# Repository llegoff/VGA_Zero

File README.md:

[:fr:](LISEZMOI.md) [:uk:](README.md)

# VGA_Zero
VGA interface for Raspberry Pi Zéro &amp; 2,3,B+

for pi400 see https://github.com/llegoff/Pi400VGA

buy rev3 on [ebay](https://www.ebay.fr/itm/154857982971) :package:

### DPI (Display parallel Interface)
Like [VGA666](https://github.com/fenlogic/vga666), this pcb uses dpi interface (in mode 3 to free gpio 18 & 19)

see https://www.raspberrypi.org/documentation/hardware/raspberrypi/dpi/README.md

only the necessary bits of the dpi are redirected to the 40-pin GPIO port, with the [vga565.dtbo](overlays/vga565.dtbo?raw=true) file loaded at startup

here is the code of the file:

    /dts-v1/;
    /plugin/;
    /{
    	compatible = "brcm,bcm2708";
    	// There is no VGA driver module, but we need a platform device
    	// node (that doesn't already use pinctrl) to hang the pinctrl
    	// reference on - leds will do
    	fragment@0 {
    		target = <&leds>;
    		__overlay__ {
    			pinctrl-names = "default";
    			pinctrl-0 = <&vga565_pins>;
    		};
	    };
    	fragment@1 {
    		target = <&gpio>;
    		__overlay__ {
    			vga565_pins: vga565_pins {
        			brcm,pins = <2 3 4 5 6 7 8 12 13 14 15 16 17 20 21 22 23 24>;
    				brcm,function = <6>; /* alt2 */
				    brcm,pull = <0>; /* no pull */
			    };
		    };
	    };
    };

/boot/config.txt
    
    # disable i2c, pin use by h-sync & v-sync
    dtparam=i2c_arm=off
    dtoverlay=vga565
    dpi_output_format=0x13
    enable_dpi_lcd=1
    display_default_lcd=1
    dpi_group=2
    dpi_mode=16
    #---------------- dpi_mode line ---------------------
    #---> 640x480 60hz    dpi_mode=4
    #---> 800x600 60hz    dpi_mode=9
    #---> 1024x768 60hz   dpi_mode=16
    #---> 1280x768 60hz   dpi_mode=23
    #---> 1280x800 60hz   dpi_mode=28
    #---> 1280x960 60hz   dpi_mode=32
    #---> 1280x1024 60hz  dpi_mode=35
    #---> 1360x768 60hz   dpi_mode=39
    #---> 1366x768 60hz   dpi_mode=81
    #---> 1400x1050 60hz  dpi_mode=42
    #---> 1440x900 60hz   dpi_mode=47
    #---> 1600x1200 60hz  dpi_mode=51
    #---> 1680x1050 60hz  dpi_mode=58
    #---> 1920x1080 60hz  dpi_mode=82
    #---> 1920x1200 60hz  dpi_mode=69
    #---> 1920x1440 60hz  dpi_mode=73

alternate config, no need dtbo file

    # replace dtoverlay=vc4-kms-v3d with
    dtoverlay=vc4-fkms-v3d
    # disable i2c, pin use by h-sync & v-sync
    dtparam=i2c_arm=off
    gpio=2-8,12-17,20-24=a2
    dpi_output_format=0x13
    enable_dpi_lcd=1
    display_default_lcd=1
    dpi_group=2
    dpi_mode=16
    #---------------- dpi_mode line ---------------------
    #---> 640x480 60hz    dpi_mode=4
    #---> 800x600 60hz    dpi_mode=9
    #---> 1024x768 60hz   dpi_mode=16
    #---> 1280x768 60hz   dpi_mode=23
    #---> 1280x800 60hz   dpi_mode=28
    #---> 1280x960 60hz   dpi_mode=32
    #---> 1280x1024 60hz  dpi_mode=35
    #---> 1360x768 60hz   dpi_mode=39
    #---> 1366x768 60hz   dpi_mode=81
    #---> 1400x1050 60hz  dpi_mode=42
    #---> 1440x900 60hz   dpi_mode=47
    #---> 1600x1200 60hz  dpi_mode=51
    #---> 1680x1050 60hz  dpi_mode=58
    #---> 1920x1080 60hz  dpi_mode=82
    #---> 1920x1200 60hz  dpi_mode=69
    #---> 1920x1440 60hz  dpi_mode=73

Configuration working with vc4-kms-v3d

    dtoverlay=vc4-kms-dpi-generic,rgb565-padhi
    dtparam=hactive=800,hfp=40,hsync=128,hbp=88
    dtparam=vactive=600,vfp=1,vsync=4,vbp=23
    dtparam=clock-frequency=40000000
    #   Resolution@freq  hactive hfp hsync  hbp vactive vfp vsync vbp  clock-frequency
    #VGA   640x480  @60   640     16   96    48   480    10   2    33    25175000
    #SVGA  800x600  @60   800     40  128    88   600     1   4    23    40000000
    #XGA  1024x768  @60  1024     24  136   160   768     3   6    29    65000000
    #VESA 1368x768  @60  1368     72  144   216   768     1   3    23    85860000
    #VESA 1280x800  @60  1280     64  136   200   800     1   3    24    83460000
    #VESA 1280x1024 @60  1280     48  112   248  1024     1   3    38   108000000
    #VESA 1400x1050 @60  1400     88  152   240  1050     1   3    33   122660000
    #VESA 1600x1200 @60  1600     64  192   304  1200     1   3    46   162000000
    #--- TV -----
    #244p (NTSC res)@60   320      4   30    46   240     4   5    14     6400000
    #288p (PAL res) @50   384     16   32    40   288     3   2    19     7363200
    #480i (NTSC res)@60   640     24   64   104   480     3   6    34    13054080
    #576i (PAL res) @50   768     24   72    88   576     6   5    38    14875000
    #480p           @60   640     24   96    48   480    11   2    32    25452000
    #720p           @60  1280    110   40   220   720     5   5    20    74250000
    #1080p          @60  1920     88   44   148  1080     4   5    36   148500000
    #more timming on http://tinyvga.com/vga-timing

### 15khz cathode ray screen

    # disable i2c, pin use by h-sync & v-sync
    dtparam=i2c_arm=off
    gpio=2-8,12-17,20-24=a2
    dpi_output_format=0x13
    enable_dpi_lcd=1
    display_default_lcd=1
    dpi_group=2
    dpi_mode=87
    #hdmi_timings=506 1 8 48 56 240 1 3 10 6 0 0 0 60 0 9600000 1
    #hdmi_timings=512 1 16 48 64 288 1 3 5 6 0 0 0 50 0 9600000 1
    # Custom 15kHz mode
    hdmi_timings=506 1 8 44 52 240 1 6 10 6 0 0 0 60 0 9600000 1
    #hdmi_timings=320 1 17 33 34 224 1 14 8 18 0 0 0 60 0 6400000 1
    #hdmi_timings=960 0 173 8 0 160 0 40 10 0 0 0 0 60 0 19200000 8
    #hdmi_timings=320 1 25 30 30 240 1 9 3 10 0 0 0 60 0 6400000 1
    #hdmi_timings=1920 1 52 208 260 240 1 6 10 6 0 0 0 60 0 38400000 1
    
for recalbox see https://recalbox.gitbook.io/tutorials/v/francais/video/crt/configurez-votre-ecran-cathodique-sur-le-bus-dpi-vga666-piscart-rgbpi

### Dual Screen (VGA + HDMI)

on the pi4 and pi400, the dual screen function is supported by the vc4 fkms v3d driver

    [pi4]
    # Enable DRM VC4 V3D driver on top of the dispmanx display stack
    dtoverlay=vc4-fkms-v3d
    max_framebuffers=2
    
for previous versions:

:warning: need raspbian buster

edit file /boot/config.txt  

at the end of the file, add line:

    [all]
    #dtoverlay=vc4-fkms-v3d
    max_framebuffers=2

edit file /usr/share/X11/xorg.conf.d/99-fbturbo.conf

     This is a minimal sample config file, which can be copied to
    # /etc/X11/xorg.conf in order to make the Xorg server pick up
    # and load xf86-video-fbturbo driver installed in the system.    
    #
    # When troubleshooting, check /var/log/Xorg.0.log for the debugging
    # output and error messages.
    #
    # Run "man fbturbo" to get additional information about the extra
    # configuration options for tuning the driver.
    
    #Section "Device"
    #        Identifier      "Allwinner A10/A13 FBDEV"
    #        Driver          "fbturbo"
    #        Option          "fbdev" "/dev/fb0"
    #        Option          "SwapbuffersWait" "true"
    #EndSection
    
    Section "Device"
    Identifier "Raspberry Pi HDMI"
    Driver "fbturbo"
    Option "fbdev" "/dev/fb0"
    Option "ShadowFB" "off"
    EndSection
    
    Section "Device"
    Identifier "Raspberry Pi DPI"
    Driver "fbturbo"
    Option "fbdev" "/dev/fb1"
    Option "ShadowFB" "off"
    EndSection
    
    Section "Monitor"
    Identifier "HDMI"
    EndSection

    Section "Monitor"
    Identifier "DPI"
    EndSection
    
    Section "Screen"
    Identifier "screen0"
    Device "Raspberry Pi HDMI"
    Monitor "HDMI"
    EndSection
    
    Section "Screen"
    Identifier "screen1"
    Device "Raspberry Pi DPI"
    Monitor "DPI"
    EndSection
    
    Section "ServerLayout"
    Identifier "default"
    Screen 0 "screen0" 0 0
    Screen 1 "screen1" RightOf "screen0"
    Option "Xinerama" "on"
    EndSection
### Remote Desktop MultiMonitor
install freeRDP

    sudo apt-get install freerdp2-x11

start freeRDP session
    
    xfreerdp /v:<computer name or IP> /u:<user> /d:<domain> /sound:sys:alsa /multimon

or

    xfreerdp /v:<computer name or IP> /u:<user> /d:<domain> /g:<gateway name or IP> /gu:<gateway user> /gd:<gateway domain> /sound:sys:alsa /multimon

### Audio Interface
audio interface is connected to gpio 18 & 19 (PWM)

see https://learn.adafruit.com/adding-basic-audio-ouput-to-raspberry-pi-zero/pi-zero-pwm-audio

/boot/config.txt

    # Enable audio for PiZero(loads snd_bcm2835)
    dtoverlay=pwm-2chan,pin=18,func=2,pin2=19,func2=2
    dtparam=audio=on

For Pi4 or Pi400 use audremap overlay

/boot/config.txt

    # Enable audio for PiZero(loads snd_bcm2835)
    dtoverlay=audremap,pins_18_19
    dtparam=audio=on

### SPI Interface
GPIO 9 , 10, 11 , 25, 26, 27 can be used as SPI , whit overlay spi0-cs, with CS redirection to gpio 26 & 27

/boot/config.txt

    # uncomment to use spi0 with cs0 & cs1 retirected on pin 26 & 27 
    dtparam=spi=on
    dtoverlay=spi0-cs,cs0_pin=26,cs1_pin=27

## Schematic

## PCB

## Installation
Copy [vga565.dtbo](overlays/vga565.dtbo?raw=true) to /boot/overlays/
and copy content of [config-example.txt](overlays/config-example.txt?raw=true) to /boot/config.txt

## Révision
rev1
- bad vga footprint, hole too small

rev2
- change vga footprint
- move j3 & j5

rev3
- add GPIO25 to J4 connector
- add j6 DC 3.5x1.3 connector
- change to Kicad v5.0.2 lib

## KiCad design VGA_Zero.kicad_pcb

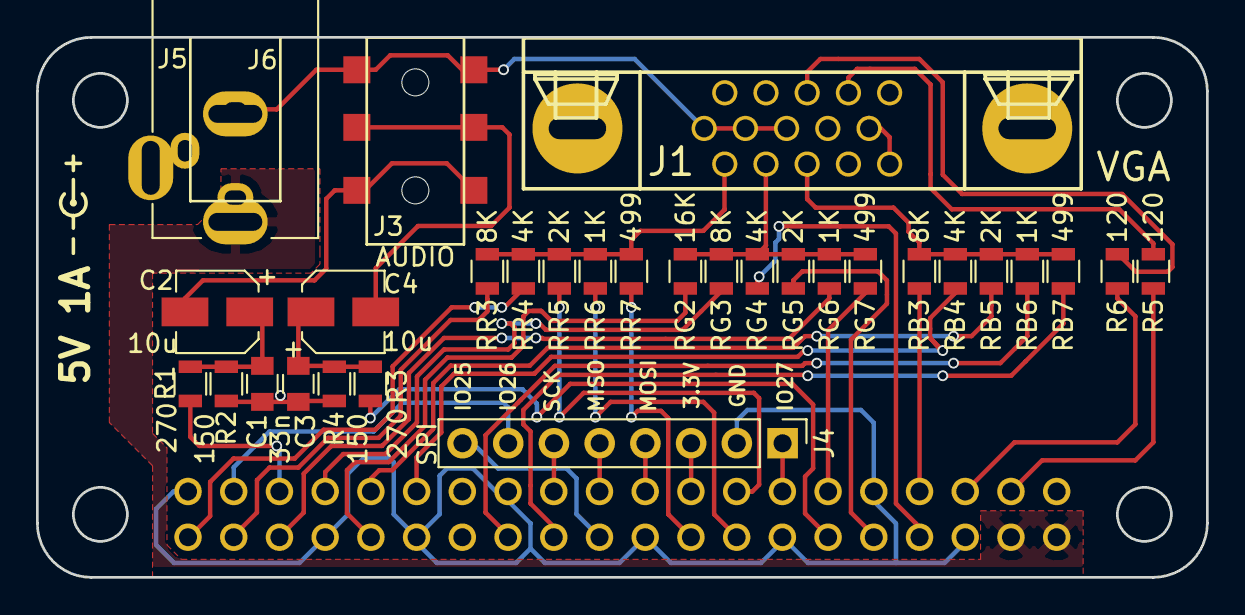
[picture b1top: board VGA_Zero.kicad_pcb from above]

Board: 2 copper layers, 65.0 x 30.0 mm, 32 parts (0 on the bottom side), 38 nets.

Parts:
C1, C3: 33n; C_0805
C2, C4: 10u; CP_Elec_4x5.3
J1: VGA; DB_15F-VGA
J2: CONN_02X20; RaspberryPiZeroHAT
J3: AUDIO; jack3.5smd
J4: SPI; Pin_Header_Straight_1x08_Pitch2.54mm
J5: BARREL_JACK
J6: BARREL_JACK; DC002_3.5x1.1
R1, R3: 270; R_0805
R2, R4: 150; R_0805
R5, R6: 120; R_0805
RB3: 8K; R_0805
RB4: 4K; R_0805
RB5: 2K; R_0805
RB6: 1K; R_0805
RB7: 499; R_0805
RG2: 16K; R_0805
RG3: 8K; R_0805
RG4: 4K; R_0805
RG5: 2K; R_0805
RG6: 1K; R_0805
RG7: 499; R_0805
RR3: 8K; R_0805
RR4: 4K; R_0805
RR5: 2K; R_0805
RR6: 1K; R_0805
RR7: 499; R_0805

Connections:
/3.3: J2.17, J4.3
/5V: J2.2, J2.4, J5.1, J6.1
/B3: J2.7, RB3.1
/B4: J2.29, RB4.1
/B5: J2.31, RB5.1
/B6: J2.26, RB6.1
/B7: J2.24, RB7.1
/G2: J2.32, RG2.1
/G3: J2.33, RG3.1
/G4: J2.8, RG4.1
/G5: J2.10, RG5.1
/G6: J2.36, RG6.1
/G7: J2.11, RG7.1
/H: J2.5, R6.1
/IO25: J2.22, J4.8
/IO26: J2.37, J4.7
/IO27: J2.13, J4.1
/LPWM: J2.35, R1.1
/MISO: J2.21, J4.5
/MOSI: J2.19, J4.4
/R3: J2.38, RR3.1
/R4: J2.40, RR4.1
/R5: J2.15, RR5.1
/R6: J2.16, RR6.1
/R7: J2.18, RR7.1
/RPWM: J2.12, R3.1
/SCK: J2.23, J4.6
/V: J2.3, R5.1
/VGAB: J1.3, RB3.2, RB4.2, RB5.2, RB6.2, RB7.2
/VGAG: J1.2, RG2.2, RG3.2, RG4.2, RG5.2, RG6.2, RG7.2
/VGAH: J1.13, R6.2
/VGAR: J1.1, RR3.2, RR4.2, RR5.2, RR6.2, RR7.2
/VGAV: J1.14, R5.2
GND: C1.2, C3.2, J1.5, J1.6, J1.7, J1.8, J1.10, J2.6, J2.9, J2.14, J2.20, J2.25, J2.30, J2.34, J2.39, J3.S, J4.2, J5.2, J5.3, J6.2, J6.3, R2.1, R4.1
unnamed: C1.1, C2.1, R1.2, R2.2
unnamed: C2.2, J3.T
unnamed: C3.1, C4.1, R3.2, R4.2
unnamed: C4.2, J3.R

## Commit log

2017-09-08 rev1
    warning bad vga footprint
2017-09-08 Overlay
2017-09-09 rev2
2019-02-01 rev3
2019-02-06 Kicad v5.0.2 lib
2019-02-07 Kicad 5.0.2 lib
2019-06-27 dual screen
2019-06-27 double écrans
